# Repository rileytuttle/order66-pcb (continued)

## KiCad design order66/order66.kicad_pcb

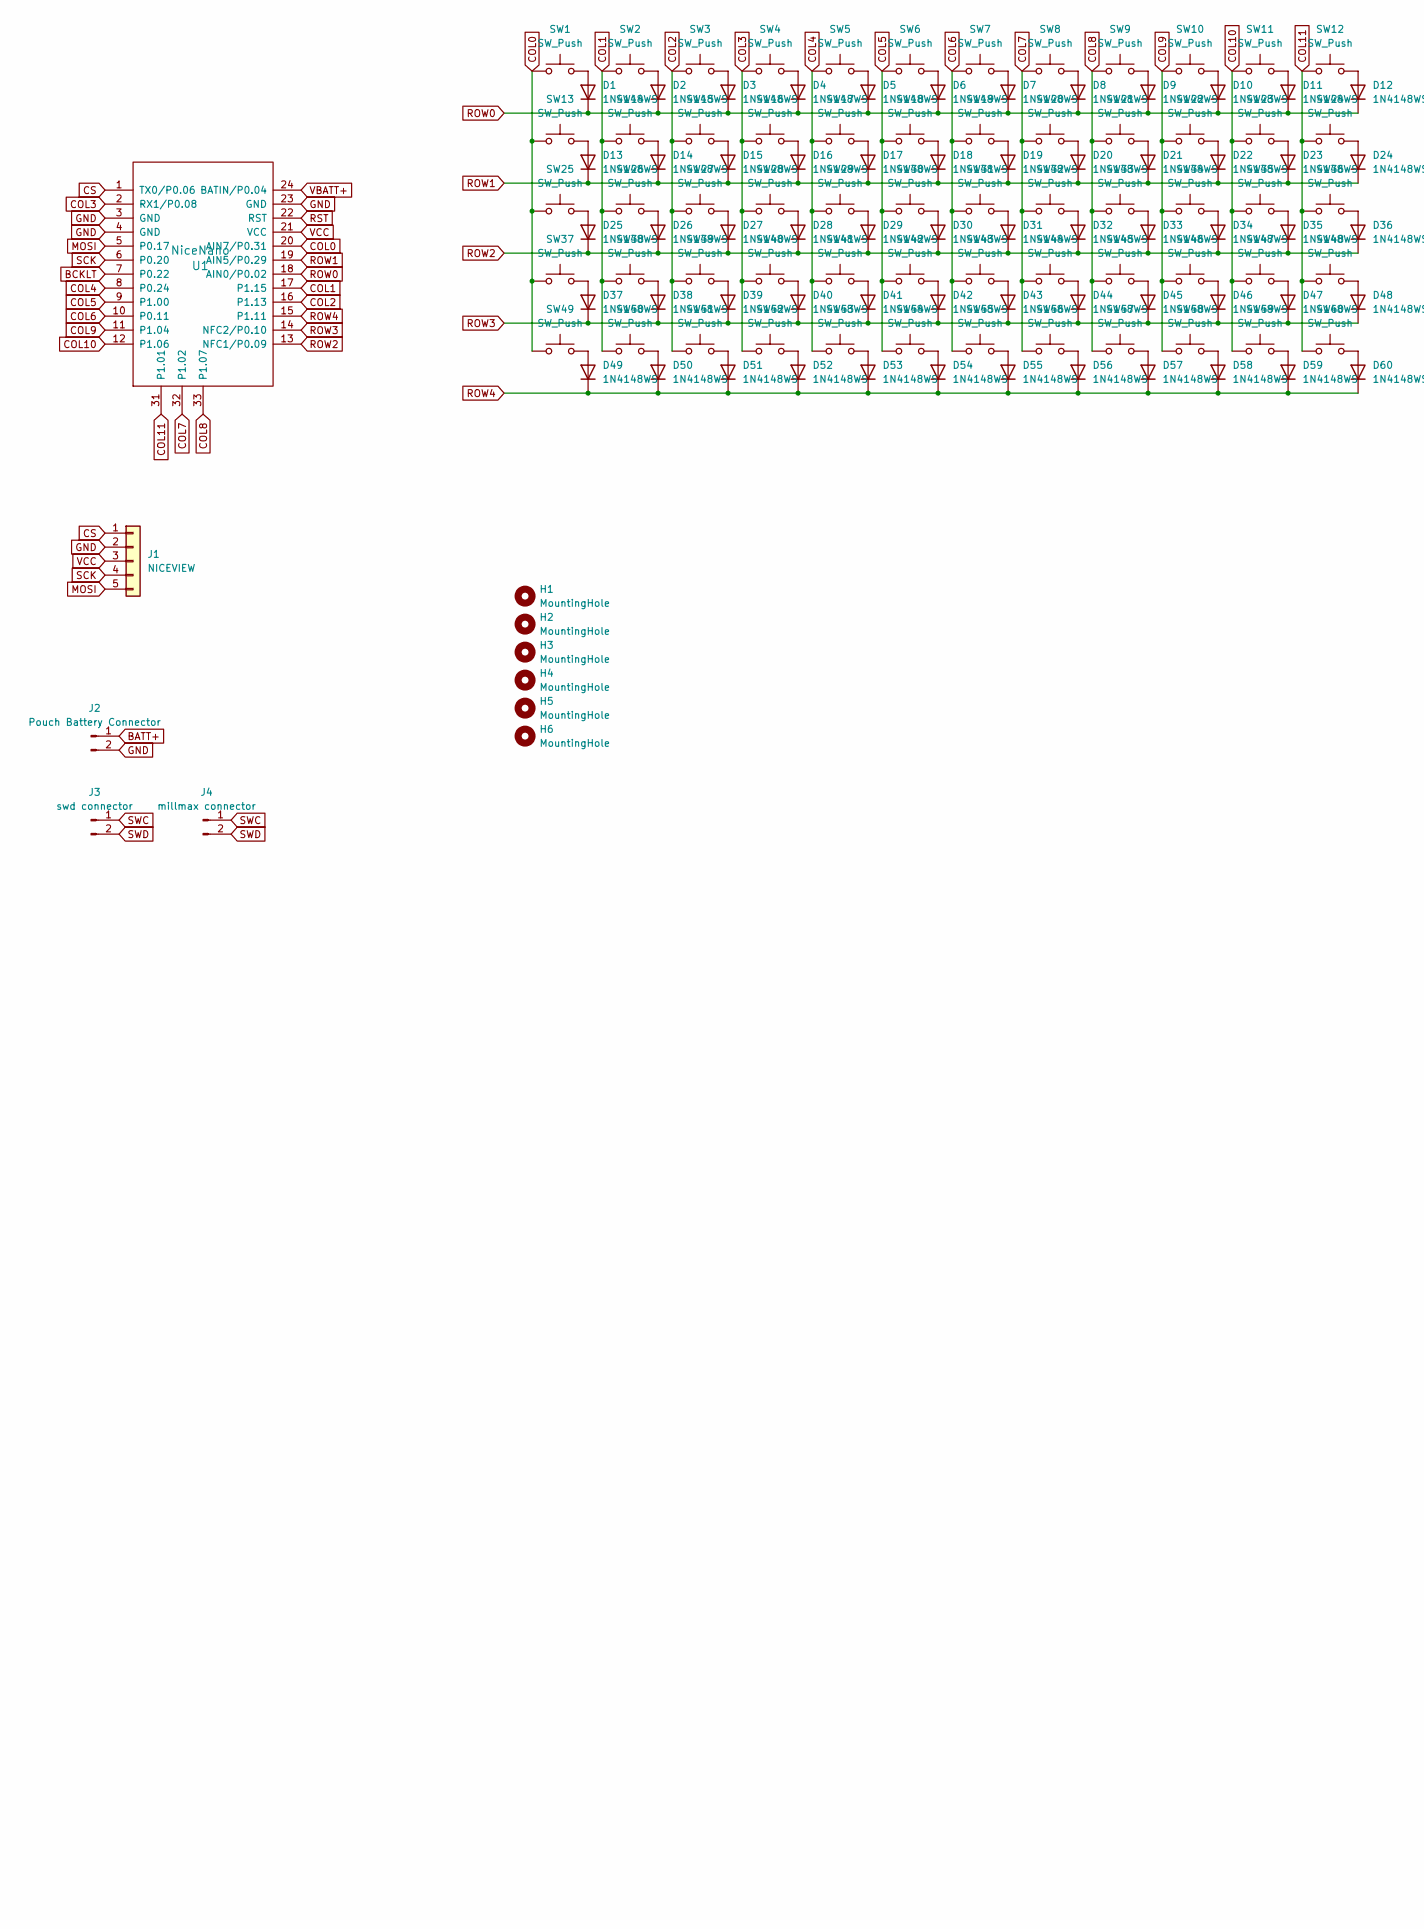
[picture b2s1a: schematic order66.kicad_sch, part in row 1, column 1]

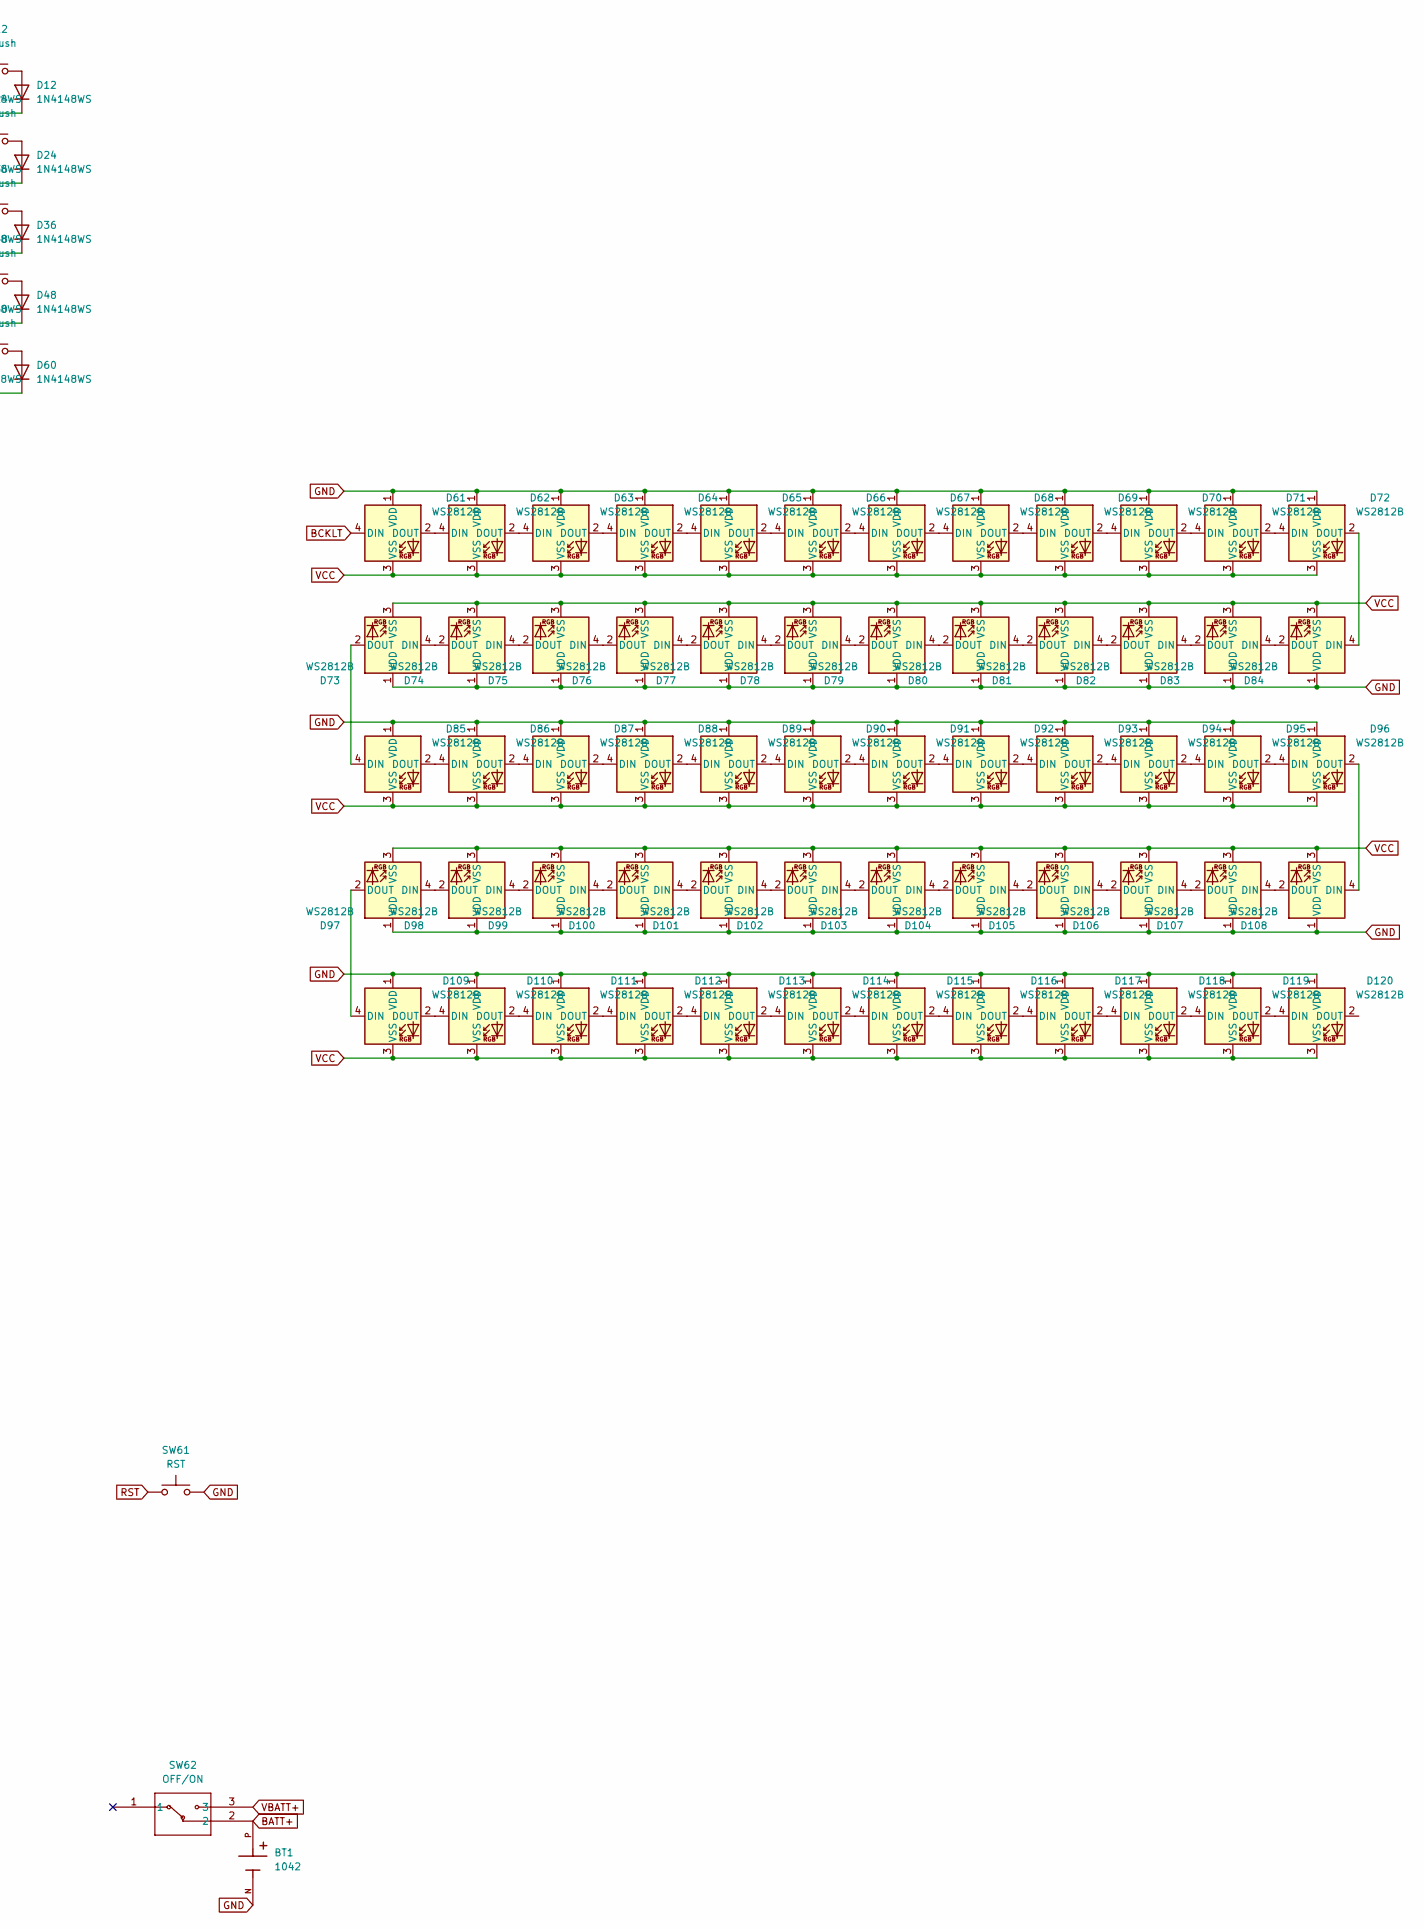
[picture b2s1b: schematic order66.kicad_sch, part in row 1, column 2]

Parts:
BT1: 1042; BAT_1043P; PARTREV D
D1, D2, D3, D4, D5, D6, D7, D8, D9, D10, D11, D12, D13, D14, D15, D16, D17, D18, D19, D20, D21, D22, D23, D24, D25, D26, D27, D28, D29, D30, D31, D32, D33, D34, D35, D36, D37, D38, D39, D40, D41, D42, D43, D44, D45, D46, D47, D48, D49, D50, D51, D52, D53, D54, D55, D56, D57, D58, D59, D60: 1N4148WS; D_SOD-323
D61, D62, D63, D64, D65, D66, D67, D68, D69, D70, D71, D72, D73, D74, D75, D76, D77, D78, D79, D80, D81, D82, D83, D84, D85, D86, D87, D88, D89, D90, D91, D92, D93, D94, D95, D96, D97, D98, D99, D100, D101, D102, D103, D104, D105, D106, D107, D108, D109, D110, D111, D112, D113, D114, D115, D116, D117, D118, D119, D120: WS2812B; LED_SK6812MINI_PLCC4_3.5x3.5mm_P1.75mm
H1, H2, H3, H4, H5, H6: MountingHole; MountingHole_2.7mm_M2.5
J1: NICEVIEW; PinHeader_1x05_P2.54mm_Vertical
J2: Pouch Battery Connector; JST_PH_B2B-PH-K_1x02_P2.00mm_Vertical
J3: swd connector; PinHeader_1x02_P2.54mm_Horizontal
J4: millmax connector; PinHeader_1x02_P2.54mm_Vertical
SW1, SW2, SW3, SW4, SW5, SW6, SW7, SW8, SW9, SW10, SW11, SW12, SW13, SW14, SW15, SW16, SW17, SW18, SW19, SW20, SW21, SW22, SW23, SW24, SW25, SW26, SW27, SW28, SW29, SW30, SW31, SW32, SW33, SW34, SW35, SW36, SW37, SW38, SW39, SW40, SW41, SW42, SW43, SW44, SW45, SW46, SW47, SW48, SW49, SW50, SW51, SW52, SW53, SW54, SW55, SW56, SW57, SW58, SW59, SW60: SW_Push; MX-Hotswap-1U
SW61: RST; SW_TH_Tactile_Omron_B3F-10xx
SW62: OFF/ON; EG1206A_EWI
U1: NiceNano; nice_nano

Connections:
BATT+: BT1.P, J2.1, SW62.2
BCKLT: D61.4 (DIN), U1.7 (P0.22)
COL0: SW1.1, SW13.1, SW25.1, SW37.1, SW49.1, U1.20 (AIN7/P0.31)
COL1: SW2.1, SW14.1, SW26.1, SW38.1, SW50.1, U1.17 (P1.15)
COL2: SW3.1, SW15.1, SW27.1, SW39.1, SW51.1, U1.16 (P1.13)
COL3: SW4.1, SW16.1, SW28.1, SW40.1, SW52.1, U1.2 (RX1/P0.08)
COL4: SW5.1, SW17.1, SW29.1, SW41.1, SW53.1, U1.8 (P0.24)
COL5: SW6.1, SW18.1, SW30.1, SW42.1, SW54.1, U1.9 (P1.00)
COL6: SW7.1, SW19.1, SW31.1, SW43.1, SW55.1, U1.10 (P0.11)
COL7: SW8.1, SW20.1, SW32.1, SW44.1, SW56.1, U1.32 (P1.02)
COL8: SW9.1, SW21.1, SW33.1, SW45.1, SW57.1, U1.33 (P1.07)
COL9: SW10.1, SW22.1, SW34.1, SW46.1, SW58.1, U1.11 (P1.04)
COL10: SW11.1, SW23.1, SW35.1, SW47.1, SW59.1, U1.12 (P1.06)
COL11: SW12.1, SW24.1, SW36.1, SW48.1, SW60.1, U1.31 (P1.01)
CS: J1.1, U1.1 (TX0/P0.06)
GND: BT1.N, D61.1 (VDD), D62.1 (VDD), D63.1 (VDD), D64.1 (VDD), D65.1 (VDD), D66.1 (VDD), D67.1 (VDD), D68.1 (VDD), D69.1 (VDD), D70.1 (VDD), D71.1 (VDD), D72.1 (VDD), D73.1 (VDD), D74.1 (VDD), D75.1 (VDD), D76.1 (VDD), D77.1 (VDD), D78.1 (VDD), D79.1 (VDD), D80.1 (VDD), D81.1 (VDD), D82.1 (VDD), D83.1 (VDD), D84.1 (VDD), D85.1 (VDD), D86.1 (VDD), D87.1 (VDD), D88.1 (VDD), D89.1 (VDD), D90.1 (VDD), D91.1 (VDD), D92.1 (VDD), D93.1 (VDD), D94.1 (VDD), D95.1 (VDD), D96.1 (VDD), D97.1 (VDD), D98.1 (VDD), D99.1 (VDD), D100.1 (VDD), D101.1 (VDD), D102.1 (VDD), D103.1 (VDD), D104.1 (VDD), D105.1 (VDD), D106.1 (VDD), D107.1 (VDD), D108.1 (VDD), D109.1 (VDD), D110.1 (VDD), D111.1 (VDD), D112.1 (VDD), D113.1 (VDD), D114.1 (VDD), D115.1 (VDD), D116.1 (VDD), D117.1 (VDD), D118.1 (VDD), D119.1 (VDD), D120.1 (VDD), J1.2, J2.2, SW61.2, U1.3 (GND), U1.4 (GND), U1.23 (GND)
MOSI: J1.5, U1.5 (P0.17)
unnamed: D1.2 (A), SW1.2
unnamed: D2.2 (A), SW2.2
unnamed: D3.2 (A), SW3.2
unnamed: D4.2 (A), SW4.2
unnamed: D5.2 (A), SW5.2
unnamed: D6.2 (A), SW6.2
unnamed: D7.2 (A), SW7.2
unnamed: D8.2 (A), SW8.2
unnamed: D9.2 (A), SW9.2
unnamed: D10.2 (A), SW10.2
unnamed: D11.2 (A), SW11.2
unnamed: D12.2 (A), SW12.2
unnamed: D13.2 (A), SW13.2
unnamed: D14.2 (A), SW14.2
unnamed: D15.2 (A), SW15.2
unnamed: D16.2 (A), SW16.2
unnamed: D17.2 (A), SW17.2
unnamed: D18.2 (A), SW18.2
unnamed: D19.2 (A), SW19.2
unnamed: D20.2 (A), SW20.2
unnamed: D21.2 (A), SW21.2
unnamed: D22.2 (A), SW22.2
unnamed: D23.2 (A), SW23.2
unnamed: D24.2 (A), SW24.2
unnamed: D25.2 (A), SW25.2
unnamed: D26.2 (A), SW26.2
unnamed: D27.2 (A), SW27.2
unnamed: D28.2 (A), SW28.2
unnamed: D29.2 (A), SW29.2
unnamed: D30.2 (A), SW30.2
unnamed: D31.2 (A), SW31.2
unnamed: D32.2 (A), SW32.2
unnamed: D33.2 (A), SW33.2
unnamed: D34.2 (A), SW34.2
unnamed: D35.2 (A), SW35.2
unnamed: D36.2 (A), SW36.2
unnamed: D37.2 (A), SW37.2
unnamed: D38.2 (A), SW38.2
unnamed: D39.2 (A), SW39.2
unnamed: D40.2 (A), SW40.2
unnamed: D41.2 (A), SW41.2
unnamed: D42.2 (A), SW42.2
unnamed: D43.2 (A), SW43.2
unnamed: D44.2 (A), SW44.2
unnamed: D45.2 (A), SW45.2
unnamed: D46.2 (A), SW46.2
unnamed: D47.2 (A), SW47.2
unnamed: D48.2 (A), SW48.2
unnamed: D49.2 (A), SW49.2
unnamed: D50.2 (A), SW50.2
unnamed: D51.2 (A), SW51.2
unnamed: D52.2 (A), SW52.2
unnamed: D53.2 (A), SW53.2
unnamed: D54.2 (A), SW54.2
unnamed: D55.2 (A), SW55.2
unnamed: D56.2 (A), SW56.2
unnamed: D57.2 (A), SW57.2
unnamed: D58.2 (A), SW58.2
unnamed: D59.2 (A), SW59.2
unnamed: D60.2 (A), SW60.2
unnamed: D61.2 (DOUT), D62.4 (DIN)
unnamed: D62.2 (DOUT), D63.4 (DIN)
unnamed: D63.2 (DOUT), D64.4 (DIN)
unnamed: D64.2 (DOUT), D65.4 (DIN)
unnamed: D65.2 (DOUT), D66.4 (DIN)
unnamed: D66.2 (DOUT), D67.4 (DIN)
unnamed: D67.2 (DOUT), D68.4 (DIN)
unnamed: D68.2 (DOUT), D69.4 (DIN)
unnamed: D69.2 (DOUT), D70.4 (DIN)
unnamed: D70.2 (DOUT), D71.4 (DIN)
unnamed: D71.2 (DOUT), D72.4 (DIN)
unnamed: D72.2 (DOUT), D84.4 (DIN)
unnamed: D73.4 (DIN), D74.2 (DOUT)
unnamed: D73.2 (DOUT), D85.4 (DIN)
unnamed: D74.4 (DIN), D75.2 (DOUT)
unnamed: D75.4 (DIN), D76.2 (DOUT)
unnamed: D76.4 (DIN), D77.2 (DOUT)
unnamed: D77.4 (DIN), D78.2 (DOUT)
unnamed: D78.4 (DIN), D79.2 (DOUT)
unnamed: D79.4 (DIN), D80.2 (DOUT)
unnamed: D80.4 (DIN), D81.2 (DOUT)
unnamed: D81.4 (DIN), D82.2 (DOUT)
unnamed: D82.4 (DIN), D83.2 (DOUT)
unnamed: D83.4 (DIN), D84.2 (DOUT)
unnamed: D85.2 (DOUT), D86.4 (DIN)
unnamed: D86.2 (DOUT), D87.4 (DIN)
unnamed: D87.2 (DOUT), D88.4 (DIN)
unnamed: D88.2 (DOUT), D89.4 (DIN)
unnamed: D89.2 (DOUT), D90.4 (DIN)
unnamed: D90.2 (DOUT), D91.4 (DIN)
unnamed: D91.2 (DOUT), D92.4 (DIN)
unnamed: D92.2 (DOUT), D93.4 (DIN)
unnamed: D93.2 (DOUT), D94.4 (DIN)
unnamed: D94.2 (DOUT), D95.4 (DIN)
unnamed: D95.2 (DOUT), D96.4 (DIN)
unnamed: D97.4 (DIN), D98.2 (DOUT)
unnamed: D98.4 (DIN), D99.2 (DOUT)
unnamed: D100.4 (DIN), D101.2 (DOUT)
unnamed: D99.4 (DIN), D100.2 (DOUT)
unnamed: D101.4 (DIN), D102.2 (DOUT)
unnamed: D102.4 (DIN), D103.2 (DOUT)
unnamed: D103.4 (DIN), D104.2 (DOUT)
unnamed: D104.4 (DIN), D105.2 (DOUT)
unnamed: D105.4 (DIN), D106.2 (DOUT)
unnamed: D106.4 (DIN), D107.2 (DOUT)
unnamed: D107.4 (DIN), D108.2 (DOUT)
unnamed: D96.2 (DOUT), D108.4 (DIN)
unnamed: D97.2 (DOUT), D109.4 (DIN)
unnamed: D109.2 (DOUT), D110.4 (DIN)
unnamed: D110.2 (DOUT), D111.4 (DIN)
unnamed: D111.2 (DOUT), D112.4 (DIN)
unnamed: D112.2 (DOUT), D113.4 (DIN)
unnamed: D113.2 (DOUT), D114.4 (DIN)
unnamed: D114.2 (DOUT), D115.4 (DIN)
unnamed: D115.2 (DOUT), D116.4 (DIN)
unnamed: D116.2 (DOUT), D117.4 (DIN)
unnamed: D117.2 (DOUT), D118.4 (DIN)
unnamed: D118.2 (DOUT), D119.4 (DIN)
unnamed: D119.2 (DOUT), D120.4 (DIN)
ROW0: D1.1 (K), D2.1 (K), D3.1 (K), D4.1 (K), D5.1 (K), D6.1 (K), D7.1 (K), D8.1 (K), D9.1 (K), D10.1 (K), D11.1 (K), D12.1 (K), U1.18 (AIN0/P0.02)
ROW1: D13.1 (K), D14.1 (K), D15.1 (K), D16.1 (K), D17.1 (K), D18.1 (K), D19.1 (K), D20.1 (K), D21.1 (K), D22.1 (K), D23.1 (K), D24.1 (K), U1.19 (AIN5/P0.29)
ROW2: D25.1 (K), D26.1 (K), D27.1 (K), D28.1 (K), D29.1 (K), D30.1 (K), D31.1 (K), D32.1 (K), D33.1 (K), D34.1 (K), D35.1 (K), D36.1 (K), U1.13 (NFC1/P0.09)
ROW3: D37.1 (K), D38.1 (K), D39.1 (K), D40.1 (K), D41.1 (K), D42.1 (K), D43.1 (K), D44.1 (K), D45.1 (K), D46.1 (K), D47.1 (K), D48.1 (K), U1.14 (NFC2/P0.10)
ROW4: D49.1 (K), D50.1 (K), D51.1 (K), D52.1 (K), D53.1 (K), D54.1 (K), D55.1 (K), D56.1 (K), D57.1 (K), D58.1 (K), D59.1 (K), D60.1 (K), U1.15 (P1.11)
RST: SW61.1, U1.22 (RST)
SCK: J1.4, U1.6 (P0.20)
SWC: J3.1, J4.1
SWD: J3.2, J4.2
VBATT+: SW62.3, U1.24 (BATIN/P0.04)
VCC: D61.3 (VSS), D62.3 (VSS), D63.3 (VSS), D64.3 (VSS), D65.3 (VSS), D66.3 (VSS), D67.3 (VSS), D68.3 (VSS), D69.3 (VSS), D70.3 (VSS), D71.3 (VSS), D72.3 (VSS), D73.3 (VSS), D74.3 (VSS), D75.3 (VSS), D76.3 (VSS), D77.3 (VSS), D78.3 (VSS), D79.3 (VSS), D80.3 (VSS), D81.3 (VSS), D82.3 (VSS), D83.3 (VSS), D84.3 (VSS), D85.3 (VSS), D86.3 (VSS), D87.3 (VSS), D88.3 (VSS), D89.3 (VSS), D90.3 (VSS), D91.3 (VSS), D92.3 (VSS), D93.3 (VSS), D94.3 (VSS), D95.3 (VSS), D96.3 (VSS), D97.3 (VSS), D98.3 (VSS), D99.3 (VSS), D100.3 (VSS), D101.3 (VSS), D102.3 (VSS), D103.3 (VSS), D104.3 (VSS), D105.3 (VSS), D106.3 (VSS), D107.3 (VSS), D108.3 (VSS), D109.3 (VSS), D110.3 (VSS), D111.3 (VSS), D112.3 (VSS), D113.3 (VSS), D114.3 (VSS), D115.3 (VSS), D116.3 (VSS), D117.3 (VSS), D118.3 (VSS), D119.3 (VSS), D120.3 (VSS), J1.3, U1.21 (VCC)

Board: 2 copper layers, 194 parts (39 on the bottom side), 147 nets, no tracks yet.

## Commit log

2025-06-26 Trying though hole diodes (#1)
    * changed to through hole diodes in schematic
    * moved to more through hole components and rerouted traces
    * trying to generate bom
    * reordered the switch and diode numberings to be in order
    * fixing and checking on board design rules to match pcb fabrication
    * starting work on case
2025-06-26 Trying smd and through hole diodes same time (#2)
    * added the smd sod 123 package diode symbols. havent placed/routed all the footprints yet but seems to be okay. need to figure out what I want to do with the silkscreen references. probably should j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
    * placed all diode footprints. need to sort out the silkscreen overlaps
    * added the other version of power switch that I have as well just in case
2025-06-26 updated pcb front back images and bom
2025-06-30 adding both an order 66 logo and a connector for the jlink but that needs work
2025-06-30 removing the connector for the link for now
2025-07-01 suring up before pcb fab
2025-07-09 adding some more dimensions to the pcb to aid case design
2025-07-18 Working on case after receiving pcb (#10)
    * adds the case and keygrid
    * fixes #5: fixing the switch pass through in case
2025-07-23 5x12 with backlight wip
2025-08-04 maintenance
2025-08-19 adding a 3d printed jig to hold the pcb so that I could mill out the legs of the power switch I have
2025-08-27 Added ws2812b leds to thumb keyboard. they may be too tall. I may have to switch to the 222AMVBAR tactile switches and space everything out like a centimeter more. that would be a lot of work but wou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
2025-08-27 adding the thumb keyboard to this repo for now to share the libraries but really I should move to its own repo. I will do that another time
2025-08-27 going to try reducing the slot diam
2025-09-05 working on different switches. last commit before adding the B3F-1000 switch option and extending the x gap from 10 - 12 mm
2025-09-05 first commit after change to branch with optional B3F-1000 switches. footprint is going to be 144x60
2025-09-05 have something that looks alright. max size of 144x60mm. A little concerning how messy it is though
2025-09-05 sent out v1.0 pcb order
2025-09-05 staring removal of thumming board specific files
2025-11-05 adding the power connector 3d model
